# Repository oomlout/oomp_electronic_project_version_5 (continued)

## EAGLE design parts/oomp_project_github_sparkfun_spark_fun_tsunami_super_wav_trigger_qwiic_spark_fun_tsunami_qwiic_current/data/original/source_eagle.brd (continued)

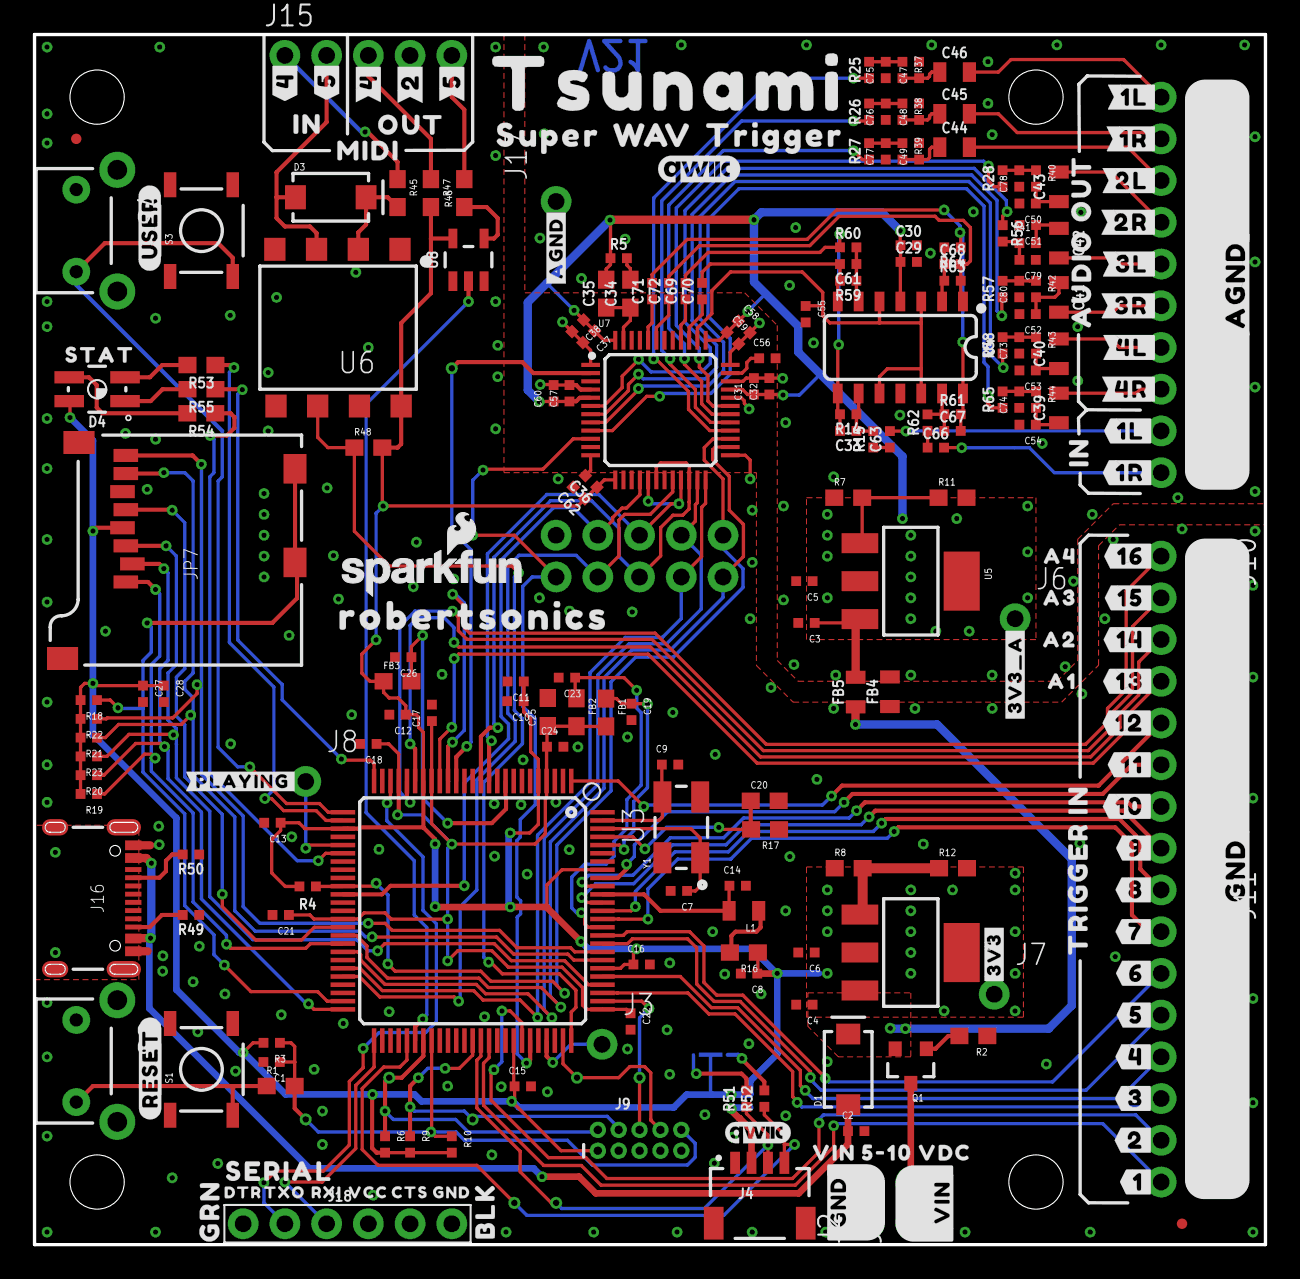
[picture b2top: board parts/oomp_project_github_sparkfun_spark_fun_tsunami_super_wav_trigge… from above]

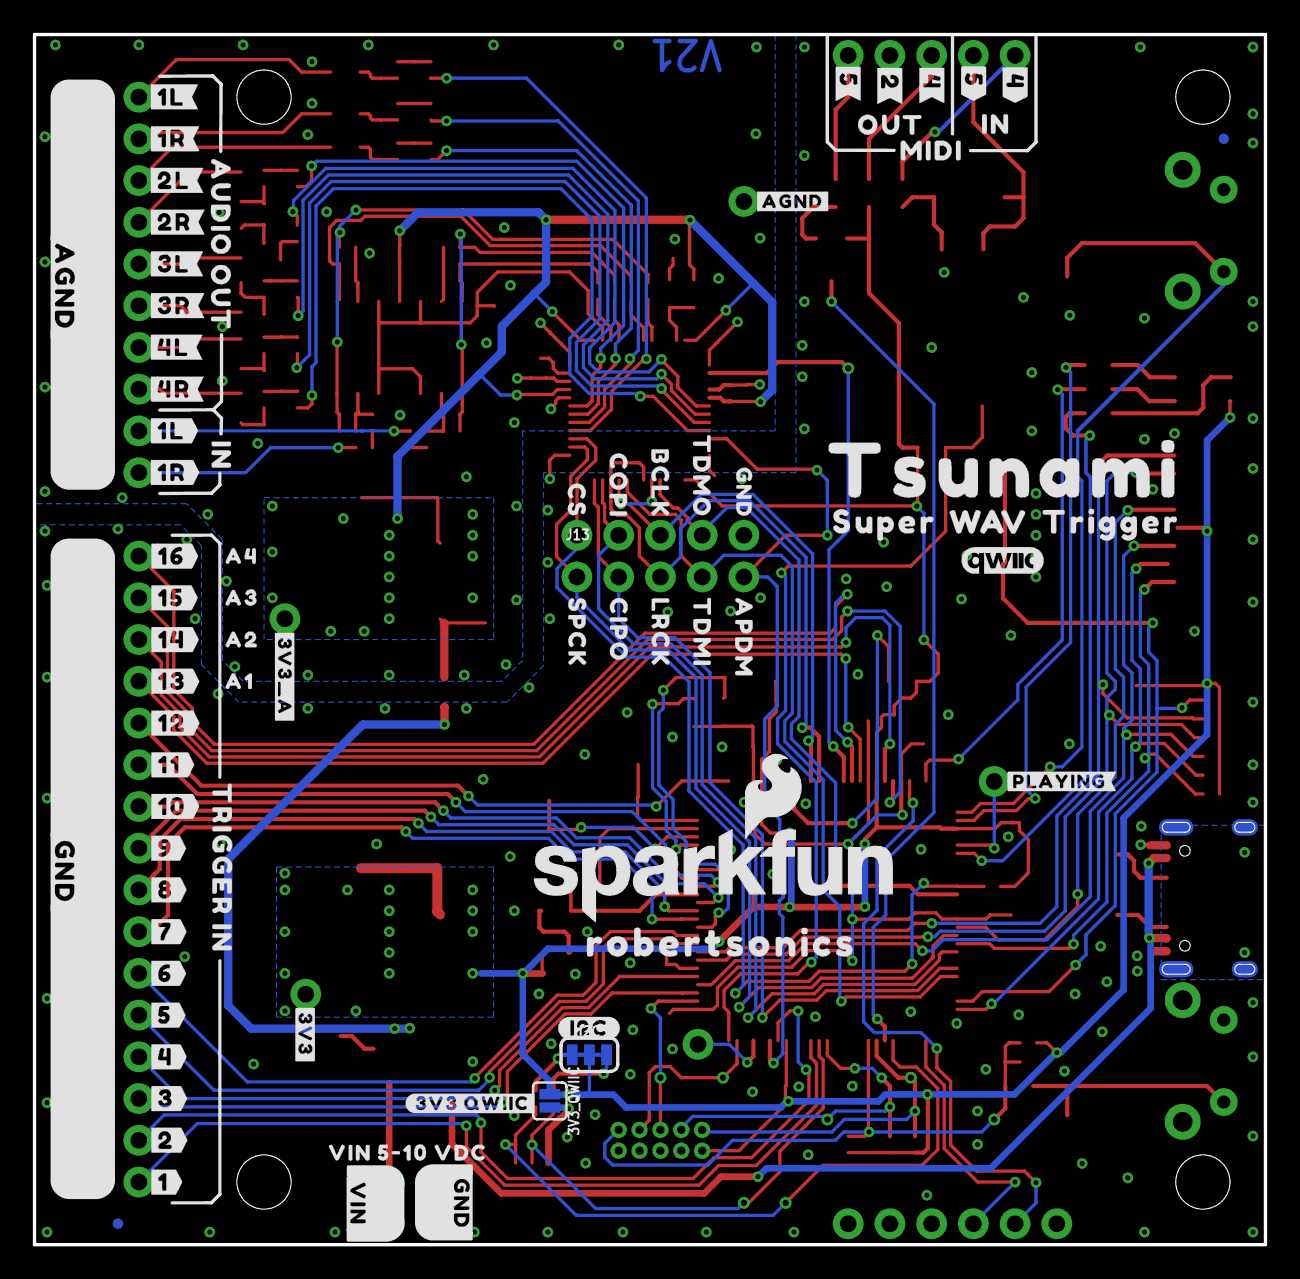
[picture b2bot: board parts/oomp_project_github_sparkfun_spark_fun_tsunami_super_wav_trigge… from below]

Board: 2 copper layers, 74.9 x 73.7 mm, 327 parts (76 on the bottom side), 138 nets.

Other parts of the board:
U$3: GND_0
U$4, U$73: QWIIC_5MM
U$5: STAT0
U$6: #USER#0
U$7: #RESET#0
U$8, U$9: ROBERTSONICS0
U$10, U$167: #2L#0
U$11: #1L#0
U$12, U$120: #1R#0
U$13: #2R#0
U$14: #3R#0
U$15: #3L#0
U$16: #4L#0
U$17: #4R#0
U$18: #4#3
U$19: #2#5
U$20, U$107: AUDIO_OUT0
U$21, U$46, U$108, U$123: IN0
U$22, U$106: TRIGGER_IN0
U$23, U$85: #GND#0
U$24: #1#0
U$25: SERIAL3
U$26, U$60: SUPER0
U$27, U$99: VIN_5#10_VDC0
U$28, U$84: #AGND#0
U$29: #2#0
U$30: #3#0
U$31, U$56, U$117: #4#0
U$32, U$58, U$118: #5#0
U$33: #6#0
U$34: #7#0
U$35: #8#0
U$36: #9#0
U$37: #10#0
U$38: #11#0
U$39: #12#0
U$40: #PLAYING#30
U$41, U$112: #3V3#0
U$43: #13#0
U$44: #3V3_A#0
U$45, U$122: MIDI0
U$47, U$124: OUT0
U$48: #14#0
U$49: #15#0
U$50: #16#0
U$51: A10
U$52: A20
U$53: A30
U$54: A40
U$55: #5#6
U$57: #2#6
U$59: #4#6
U$61, U$110: #GND#1
U$62, U$68: TRIGGER0
U$63, U$69: TSUNAMI0
U$64, U$70: W0
U$65, U$71: A0
U$66, U$72: V0
U$67, U$111: #VIN#2
U$74: #16#5
U$75: #15#17
U$76: #14#17
U$77: #13#17
U$78: #12#17
U$79: #11#17
U$80: #10#17
U$81: #9#17
U$82: #8#17
U$83: #7#17
U$86: CS17
U$87: BCLK19
U$88: COPI18
U$89: TDMO20
U$91: SPCK22
U$92: TDMI25
U$93: LRCK24
U$94: CIPO23
U$95: APDM26
U$96: #AGND#27
U$97: #AGND#28
U$98: #PLAYING#29
U$102: A117
U$103: A2118
U$104: A32119
U$105: A432120
U$113: #I2C#6
U$116: #1L#3
U$119: #1L#6
U$121: #1R#2
U$141: SFE_LOGO_NAME_FLAME_.1
U$162: #3V3_A#4
U$163: #3V3_QWIIC#0
U$164: #1R#3
U$165: #5#5
U$166: #1L#2
U$168: #2R#3
U$169: #3L#3
U$170: #3R#4
U$171: #4L#4
U$172: #4R#5
U$173: #6#17
U$174: #5#17
U$175: #4#17
U$176: #3#17
U$177: #2#17
U$178: #1#17

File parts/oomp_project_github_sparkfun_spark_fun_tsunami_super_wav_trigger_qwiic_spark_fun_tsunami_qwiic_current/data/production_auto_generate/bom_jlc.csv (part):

Comment,Designator,Footprint,LCSC Part #
,U$24,SparkFun_Tsunami_Qwiic-import-fps:#1#0,
,U$178,SparkFun_Tsunami_Qwiic-import-fps:#1#17,
,U$37,SparkFun_Tsunami_Qwiic-import-fps:#10#0,
,U$80,SparkFun_Tsunami_Qwiic-import-fps:#10#17,
,U$38,SparkFun_Tsunami_Qwiic-import-fps:#11#0,
,U$79,SparkFun_Tsunami_Qwiic-import-fps:#11#17,
,U$39,SparkFun_Tsunami_Qwiic-import-fps:#12#0,
,U$78,SparkFun_Tsunami_Qwiic-import-fps:#12#17,
,U$43,SparkFun_Tsunami_Qwiic-import-fps:#13#0,
,U$77,SparkFun_Tsunami_Qwiic-import-fps:#13#17,
,U$48,SparkFun_Tsunami_Qwiic-import-fps:#14#0,
,U$76,SparkFun_Tsunami_Qwiic-import-fps:#14#17,
,U$49,SparkFun_Tsunami_Qwiic-import-fps:#15#0,
,U$75,SparkFun_Tsunami_Qwiic-import-fps:#15#17,
,U$50,SparkFun_Tsunami_Qwiic-import-fps:#16#0,
,U$74,SparkFun_Tsunami_Qwiic-import-fps:#16#5,
,U$11,SparkFun_Tsunami_Qwiic-import-fps:#1L#0,
,U$166,SparkFun_Tsunami_Qwiic-import-fps:#1L#2,
,U$116,SparkFun_Tsunami_Qwiic-import-fps:#1L#3,
,U$119,SparkFun_Tsunami_Qwiic-import-fps:#1L#6,
,"U$12,U$120",SparkFun_Tsunami_Qwiic-import-fps:#1R#0,
,U$121,SparkFun_Tsunami_Qwiic-import-fps:#1R#2,
,U$164,SparkFun_Tsunami_Qwiic-import-fps:#1R#3,
,U$29,SparkFun_Tsunami_Qwiic-import-fps:#2#0,
,U$177,SparkFun_Tsunami_Qwiic-import-fps:#2#17,
,U$19,SparkFun_Tsunami_Qwiic-import-fps:#2#5,
,U$57,SparkFun_Tsunami_Qwiic-import-fps:#2#6,
,"U$10,U$167",SparkFun_Tsunami_Qwiic-import-fps:#2L#0,
,U$13,SparkFun_Tsunami_Qwiic-import-fps:#2R#0,
,U$168,SparkFun_Tsunami_Qwiic-import-fps:#2R#3,
,U$30,SparkFun_Tsunami_Qwiic-import-fps:#3#0,
,U$176,SparkFun_Tsunami_Qwiic-import-fps:#3#17,
,U$15,SparkFun_Tsunami_Qwiic-import-fps:#3L#0,
,U$169,SparkFun_Tsunami_Qwiic-import-fps:#3L#3,
,U$14,SparkFun_Tsunami_Qwiic-import-fps:#3R#0,
,U$170,SparkFun_Tsunami_Qwiic-import-fps:#3R#4,
,"U$41,U$112",SparkFun_Tsunami_Qwiic-import-fps:#3V3#0,
,U$44,SparkFun_Tsunami_Qwiic-import-fps:#3V3_A#0,
,U$162,SparkFun_Tsunami_Qwiic-import-fps:#3V3_A#4,
,U$163,SparkFun_Tsunami_Qwiic-import-fps:#3V3_QWIIC#0,
,"U$31,U$56,U$117",SparkFun_Tsunami_Qwiic-import-fps:#4#0,
,U$175,SparkFun_Tsunami_Qwiic-import-fps:#4#17,
,U$18,SparkFun_Tsunami_Qwiic-import-fps:#4#3,
,U$59,SparkFun_Tsunami_Qwiic-import-fps:#4#6,
,U$16,SparkFun_Tsunami_Qwiic-import-fps:#4L#0,
,U$171,SparkFun_Tsunami_Qwiic-import-fps:#4L#4,
,U$17,SparkFun_Tsunami_Qwiic-import-fps:#4R#0,
,U$172,SparkFun_Tsunami_Qwiic-import-fps:#4R#5,
,"U$32,U$58,U$118",SparkFun_Tsunami_Qwiic-import-fps:#5#0,
,U$174,SparkFun_Tsunami_Qwiic-import-fps:#5#17,
,U$165,SparkFun_Tsunami_Qwiic-import-fps:#5#5,
,U$55,SparkFun_Tsunami_Qwiic-import-fps:#5#6,
,U$33,SparkFun_Tsunami_Qwiic-import-fps:#6#0,
,U$173,SparkFun_Tsunami_Qwiic-import-fps:#6#17,
,U$34,SparkFun_Tsunami_Qwiic-import-fps:#7#0,
,U$83,SparkFun_Tsunami_Qwiic-import-fps:#7#17,
,U$35,SparkFun_Tsunami_Qwiic-import-fps:#8#0,
,U$82,SparkFun_Tsunami_Qwiic-import-fps:#8#17,
,U$36,SparkFun_Tsunami_Qwiic-import-fps:#9#0,
,U$81,SparkFun_Tsunami_Qwiic-import-fps:#9#17,
,"U$28,U$84",SparkFun_Tsunami_Qwiic-import-fps:#AGND#0,
,U$96,SparkFun_Tsunami_Qwiic-import-fps:#AGND#27,
,U$97,SparkFun_Tsunami_Qwiic-import-fps:#AGND#28,
,"U$23,U$85",SparkFun_Tsunami_Qwiic-import-fps:#GND#0,
,"U$61,U$110",SparkFun_Tsunami_Qwiic-import-fps:#GND#1,
,U$113,SparkFun_Tsunami_Qwiic-import-fps:#I2C#6,
,U$98,SparkFun_Tsunami_Qwiic-import-fps:#PLAYING#29,
,U$40,SparkFun_Tsunami_Qwiic-import-fps:#PLAYING#30,
,U$7,SparkFun_Tsunami_Qwiic-import-fps:#RESET#0,
,U$6,SparkFun_Tsunami_Qwiic-import-fps:#USER#0,
,"U$67,U$111",SparkFun_Tsunami_Qwiic-import-fps:#VIN#2,
,J13,SparkFun_Tsunami_Qwiic-import-fps:2X5_NOSILK,
,J18,SparkFun_Tsunami_Qwiic-import-fps:6_PIN_SERIAL_TARGET_SIDE_W_SILK,
,"U$65,U$71",SparkFun_Tsunami_Qwiic-import-fps:A0,
,U$51,SparkFun_Tsunami_Qwiic-import-fps:A10,
,U$102,SparkFun_Tsunami_Qwiic-import-fps:A117,
,U$52,SparkFun_Tsunami_Qwiic-import-fps:A20,
,U$103,SparkFun_Tsunami_Qwiic-import-fps:A2118,
,U$53,SparkFun_Tsunami_Qwiic-import-fps:A30,
,U$104,SparkFun_Tsunami_Qwiic-import-fps:A32119,
,U$54,SparkFun_Tsunami_Qwiic-import-fps:A40,
,U$105,SparkFun_Tsunami_Qwiic-import-fps:A432120,
,U$95,SparkFun_Tsunami_Qwiic-import-fps:APDM26,
,"U$20,U$107",SparkFun_Tsunami_Qwiic-import-fps:AUDIO_OUT0,
,U$87,SparkFun_Tsunami_Qwiic-import-fps:BCLK19,
,U$94,SparkFun_Tsunami_Qwiic-import-fps:CIPO23,
,U$88,SparkFun_Tsunami_Qwiic-import-fps:COPI18,
,U$86,SparkFun_Tsunami_Qwiic-import-fps:CS17,
,U$3,SparkFun_Tsunami_Qwiic-import-fps:GND_0,
,"U$21,U$46,U$108,U$123",SparkFun_Tsunami_Qwiic-import-fps:IN0,
,U$93,SparkFun_Tsunami_Qwiic-import-fps:LRCK24,
,"U$45,U$122",SparkFun_Tsunami_Qwiic-import-fps:MIDI0,
,"U$47,U$124",SparkFun_Tsunami_Qwiic-import-fps:OUT0,
,"U$4,U$73",SparkFun_Tsunami_Qwiic-import-fps:QWIIC_5MM,
,"U$8,U$9",SparkFun_Tsunami_Qwiic-import-fps:ROBERTSONICS0,
,U$25,SparkFun_Tsunami_Qwiic-import-fps:SERIAL3,
,U$141,SparkFun_Tsunami_Qwiic-import-fps:SFE_LOGO_NAME_FLAME_.1,
,UNK3V3_QWIIC0,SparkFun_Tsunami_Qwiic-import-fps:SMT-JUMPER_2_NO_SILK,
,I2C0,SparkFun_Tsunami_Qwiic-import-fps:SMT-JUMPER_3_2-NC_TRACE_SILK,
,U$91,SparkFun_Tsunami_Qwiic-import-fps:SPCK22,
,U$5,SparkFun_Tsunami_Qwiic-import-fps:STAT0,
,"U$26,U$60",SparkFun_Tsunami_Qwiic-import-fps:SUPER0,
,U$92,SparkFun_Tsunami_Qwiic-import-fps:TDMI25,
,U$89,SparkFun_Tsunami_Qwiic-import-fps:TDMO20,
,"U$62,U$68",SparkFun_Tsunami_Qwiic-import-fps:TRIGGER0,
,"U$22,U$106",SparkFun_Tsunami_Qwiic-import-fps:TRIGGER_IN0,
,"U$63,U$69",SparkFun_Tsunami_Qwiic-import-fps:TSUNAMI0,
,"U$66,U$72",SparkFun_Tsunami_Qwiic-import-fps:V0,
,"U$27,U$99",SparkFun_Tsunami_Qwiic-import-fps:VIN_5#10_VDC0,
,"U$64,U$70",SparkFun_Tsunami_Qwiic-import-fps:W0,
0.1uF,"C3,C4,C8,C10,C12,C13,C15,C16,C17,C18,C19,C21,C22,C23,C24,C26,C28,C29,C31,C36,C37,C47,C48,C49,C50,C51,C52,C53,C54,C55,C56,C57,C59,C73,C74,C75,C76,C77,C78,C79,C80",SparkFun_Tsunami_Qwiic-import-fps:0402-TIGHT,C60474
1.0uF,"C30,C32,C38,C58,C60,C62,C63,C66,C69,C70,C71,C72",SparkFun_Tsunami_Qwiic-import-fps:0402-TIGHT,C2887021
100,"R53,R54",SparkFun_Tsunami_Qwiic-import-fps:0603,C22775
100k,"R6,R9,R10,R19,R20,R21,R22",SparkFun_Tsunami_Qwiic-import-fps:0402-TIGHT,C25530
100pF,"C33,C61,C67,C68",SparkFun_Tsunami_Qwiic-import-fps:0402-TIGHT,
10k,"R3,R4,R18,R23",SparkFun_Tsunami_Qwiic-import-fps:0402-TIGHT,C2906861
10nF,C1,SparkFun_Tsunami_Qwiic-import-fps:0402-TIGHT,C5137480
10pF,C20,SparkFun_Tsunami_Qwiic-import-fps:0603,
10uF,"C2,C5,C6,C11,C27",SparkFun_Tsunami_Qwiic-import-fps:0402-TIGHT,C15525
10μH,L1,SparkFun_Tsunami_Qwiic-import-fps:0805,
10Ω,"R25,R26,R27,R28,R37,R38,R39,R40,R41,R42,R43,R44,R56,R57,R58,R65",SparkFun_Tsunami_Qwiic-import-fps:0402-TIGHT,C138066
11.2896 MHz,Y1,SparkFun_Tsunami_Qwiic-import-fps:CRYSTAL-OSC-SMD-5X3,
12pF,"C7,C9",SparkFun_Tsunami_Qwiic-import-fps:0402-TIGHT,
1A/40V/500mV,"D1,D3",SparkFun_Tsunami_Qwiic-import-fps:SMA-DIODE,
1M,R2,SparkFun_Tsunami_Qwiic-import-fps:0603,C2907003
2.2,R16,SparkFun_Tsunami_Qwiic-import-fps:0603,
2.2k,"R51,R52",SparkFun_Tsunami_Qwiic-import-fps:0402-TIGHT,C2906920
2.2uF,C25,SparkFun_Tsunami_Qwiic-import-fps:0603,C23630
220,"R45,R46,R47,R48,R55",SparkFun_Tsunami_Qwiic-import-fps:0603,C2907127
22uF,"C39,C40,C41,C42,C43,C44,C45,C46",SparkFun_Tsunami_Qwiic-import-fps:0805,
240,"R11,R12",SparkFun_Tsunami_Qwiic-import-fps:0603,
3.1A/30V/105mΩ,Q1,SparkFun_Tsunami_Qwiic-import-fps:SOT23-3,
3.3V,J7,SparkFun_Tsunami_Qwiic-import-fps:1X01_NO_SILK,C7501259
3.3VA,J6,SparkFun_Tsunami_Qwiic-import-fps:1X01_NO_SILK,C7501259
33,R1,SparkFun_Tsunami_Qwiic-import-fps:0603,C23140
33k,"R14,R15,R59,R60,R61,R62,R63,R64",SparkFun_Tsunami_Qwiic-import-fps:0402-TIGHT,C2909350
390,"R7,R8",SparkFun_Tsunami_Qwiic-import-fps:0603,C2907031
390nF,C35,SparkFun_Tsunami_Qwiic-import-fps:0603,
4.7uF,C14,SparkFun_Tsunami_Qwiic-import-fps:0402-TIGHT,C368809
470Ω,"FB1,FB2,FB3",SparkFun_Tsunami_Qwiic-import-fps:0603,
5.1k,"R49,R50",SparkFun_Tsunami_Qwiic-import-fps:0402-TIGHT,C25905
5.62k,R17,SparkFun_Tsunami_Qwiic-import-fps:0603,
5.6nF,C34,SparkFun_Tsunami_Qwiic-import-fps:0603,
560Ω,R5,SparkFun_Tsunami_Qwiic-import-fps:0402-TIGHT,C25126
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
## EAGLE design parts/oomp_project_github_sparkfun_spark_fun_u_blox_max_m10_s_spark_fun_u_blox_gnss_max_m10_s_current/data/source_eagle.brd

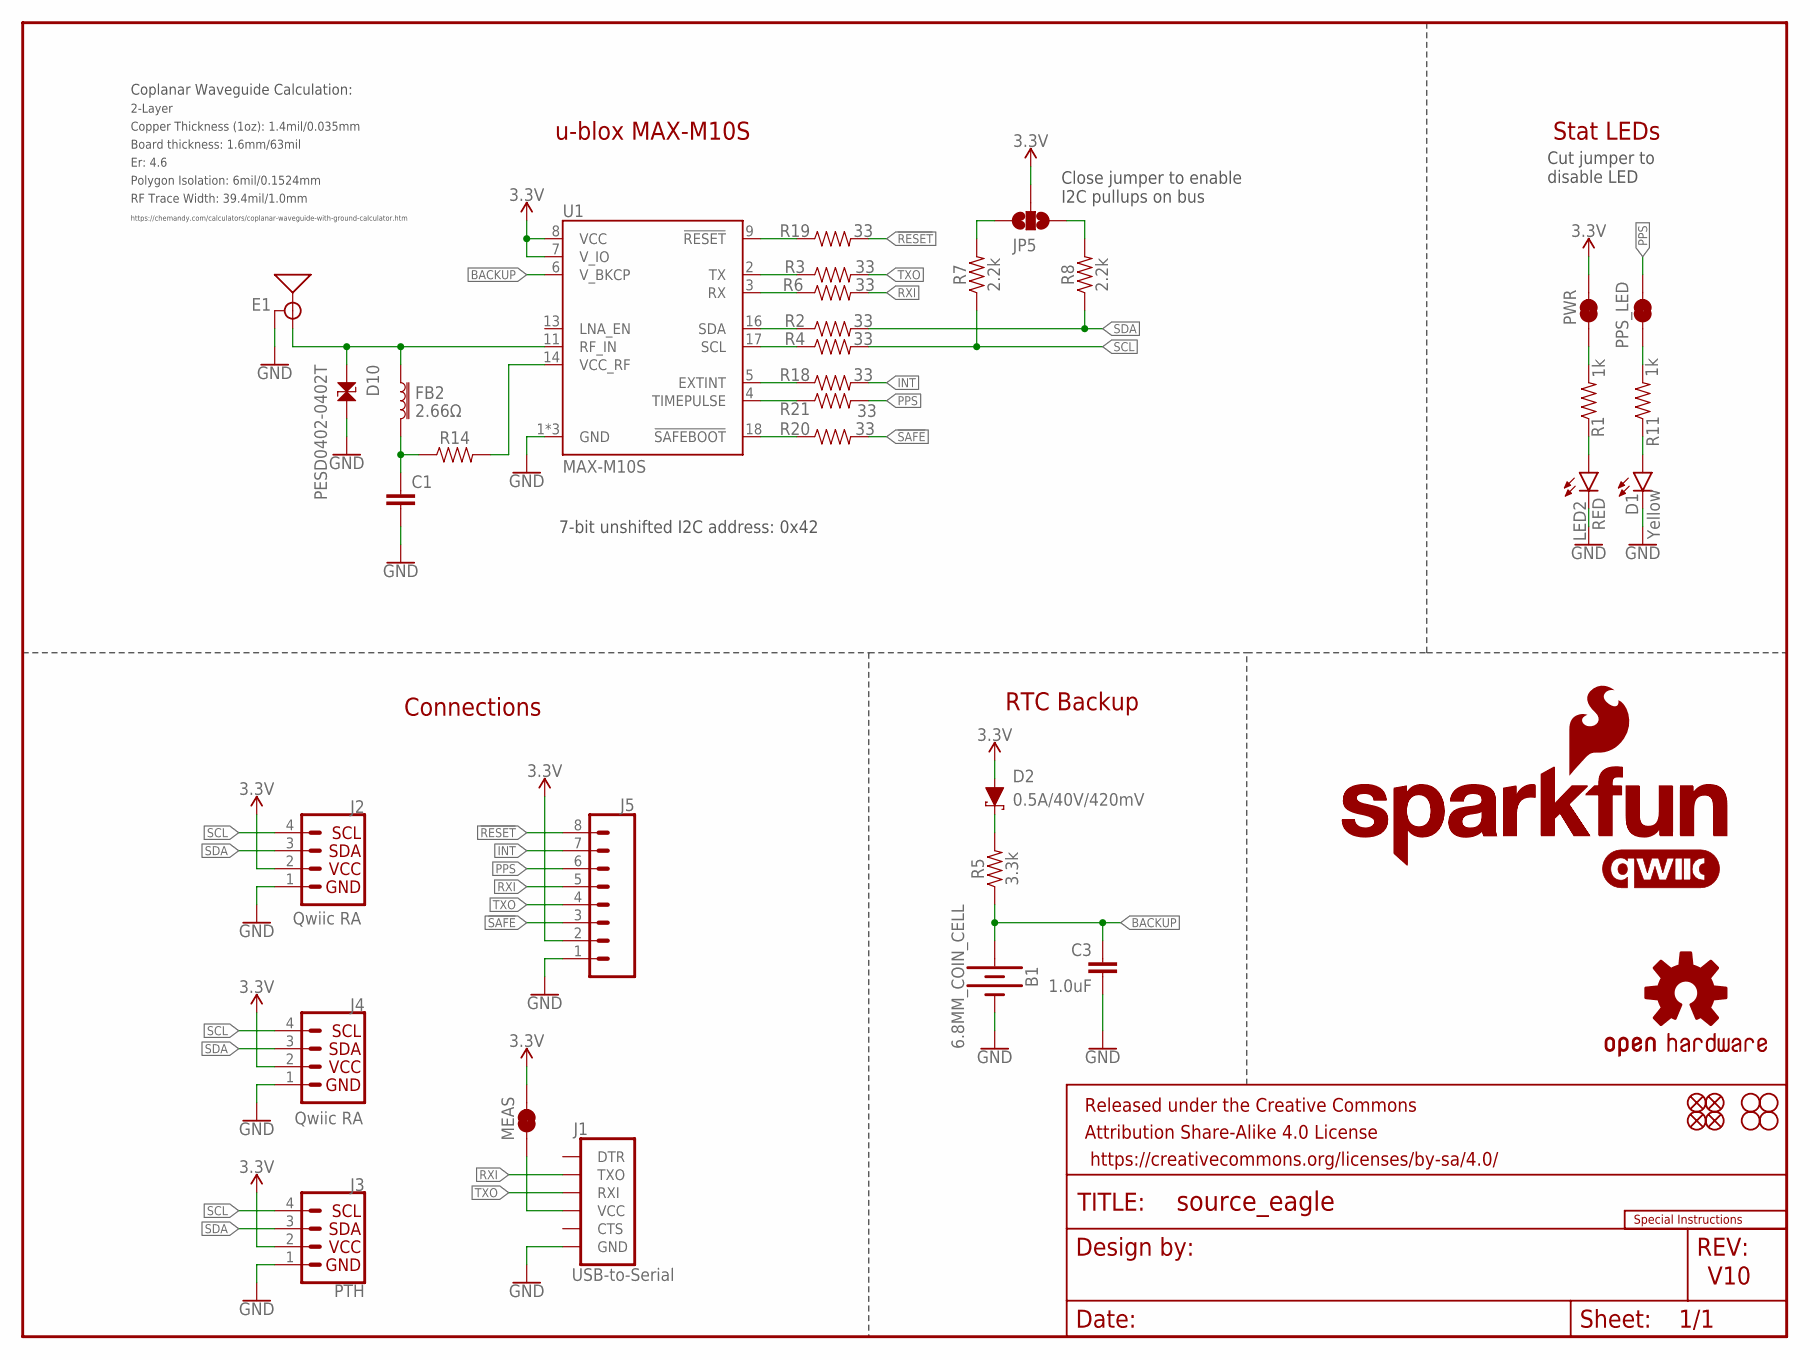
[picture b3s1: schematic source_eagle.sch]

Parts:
B1: 6.8MM_COIN_CELL; ML414H_IV01E
C1: 47pF; 0402-TIGHT
C3: 1.0uF; 0603
D1: Yellow; LED-0603
D2: 0.5A/40V/420mV; SOD-323
D10: PESD0402-0402T; 0402-TIGHT
E1: ANTENNA-SMA-GROUNDEDEDGE_SMA; SMA-EDGE
FB2: 2.66Ω; 0402-TIGHT
FD1, FD2, FD3, FD4: FIDUCIALUFIDUCIAL; FIDUCIAL-MICRO
FRAME1: FRAME-LETTER; CREATIVE_COMMONS
H1, H2, H3, H4: STAND-OFF
J1: USB-to-Serial; 1X06_NO_SILK
J2, J4: Qwiic RA; JST04_1MM_RA
J3: PTH; 1X04_NO_SILK
J5: CONN_08NO_SILK_DNP; 1X08_NO_SILK
JP5: JUMPER-SMT_3_NO_SILK; SMT-JUMPER_3_NO_SILK
LED2: RED; LED-0603
LOGO1: OSHW-LOGOMINI; OSHW-LOGO-MINI
LOGO2: SFE_LOGO_NAME_FLAME.1_INCH; SFE_LOGO_NAME_FLAME_.1
LOGO3: QWIIC_LOGO_5MM; QWIIC_5MM
LOGO4: SFE_LOGO_NAME.1_INCH; SFE_LOGO_NAME_.1
MEAS: JUMPER-COMBO_2_NC_TRACE; COMBO-JUMPER_2_NC_TRACE
PPS_LED: JUMPER-SMT_2_NC_TRACE_SILK; SMT-JUMPER_2_NC_TRACE_SILK
PWR: JUMPER-SMT_2_NC_TRACE_SILK; SMT-JUMPER_2_NC_TRACE_SILK
R1, R11: 1k; 0603
R2, R3, R4, R6, R18, R19, R20, R21: 33; 0603
R5: 3.3k; 0603
R7, R8: 2.2k; 0603
R14: 33OHM-0402T-1/10W-1%; 0402-TIGHT
U1: MAX-M10S
U$2: SPECIAL_INSTRUCTIONS-ORDERING; ORDERING_INSTRUCTIONS

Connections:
3.3V: D2.A, J2.2, J3.2 (VCC), J4.2, J5.2, JP5.2, MEAS.2, MEAS.4 (2), PWR.2, U1.7 (V_IO), U1.8 (VCC)
!RESET: J5.8, R19.2
!SAFE: J5.3, R20.2
ANT_VCC: C1.1, FB2.2, R14.1
BACKUP: B1.+, C3.1, R5.1, U1.6 (V_BKCP)
EXTINT_LV: R18.1, U1.5 (EXTINT)
GND: B1.-, C1.2, C3.2, D1.C, D10.2, E1.GND@0 (GND), E1.GND@1 (GND), E1.GND@2 (GND), E1.GND@3 (GND), J1.6 (GND), J2.1, J3.1 (GND), J4.1, J5.1, LED2.C, U1.1 (GND), U1.10 (GND), U1.12 (GND)
GPS_RF: D10.1, E1.SIG (SIGNAL), FB2.1, U1.11 (RF_IN)
INT: J5.7, R18.2
unnamed: J1.4 (VCC), MEAS.1, MEAS.3 (1)
unnamed: D1.A, R11.1
unnamed: PPS_LED.1, R11.2
unnamed: JP5.1, R8.2
unnamed: D2.C, R5.2
unnamed: JP5.3, R7.2
unnamed: LED2.A, R1.1
unnamed: PWR.1, R1.2
PPS: J5.6, PPS_LED.2, R21.2
PPS_LV: R21.1, U1.4 (TIMEPULSE)
RST_LV: R19.1, U1.9 (!RESET!)
RXI: J1.3 (TXO), J5.5, R6.2
RXLV: R6.1, U1.3 (RX)
SAFE_LV: R20.1, U1.18 (!SAFEBOOT!)
SCL: J2.4, J3.4 (SCL), J4.4, R4.2, R7.1
SCL_LV: R4.1, U1.17 (SCL)
SDA: J2.3, J3.3 (SDA), J4.3, R2.2, R8.1
SDA_LV: R2.1, U1.16 (SDA)
TXLV: R3.1, U1.2 (TX)
TXO: J1.2 (RXI), J5.4, R3.2
VCC_RF: R14.2, U1.14 (VCC_RF)

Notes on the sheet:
V10
7-bit unshifted I2C address: 0x42
u-blox MAX-M10S
RTC Backup
Stat LEDs
Close jumper to enable I2C pullups on bus
Cut jumper to disable LED
Coplanar Waveguide Calculation:
Connections
Board thickness: 1.6mm/63mil
Er: 4.6
Copper Thickness (1oz): 1.4mil/0.035mm
RF Trace Width: 39.4mil/1.0mm
Polygon Isolation: 6mil/0.1524mm
2-Layer
https://chemandy.com/calculators/coplanar-waveguide-with-ground-calculator.htm

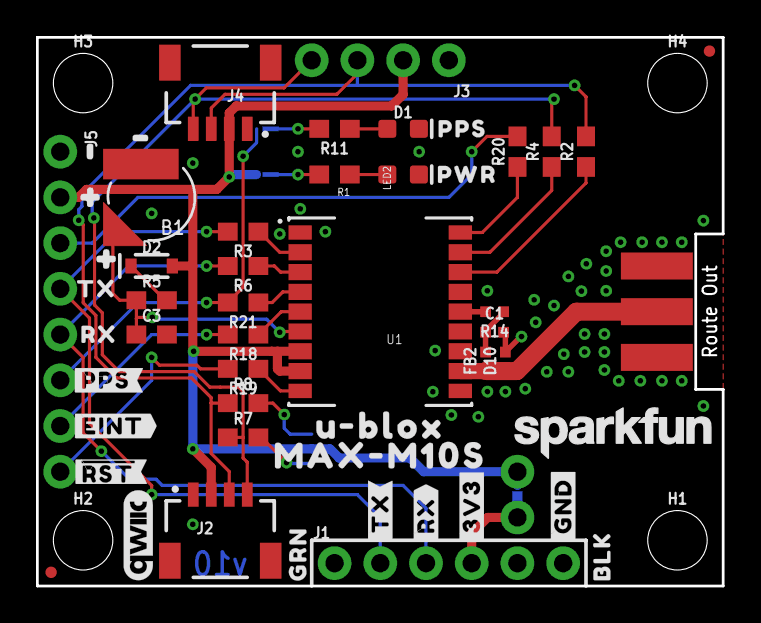
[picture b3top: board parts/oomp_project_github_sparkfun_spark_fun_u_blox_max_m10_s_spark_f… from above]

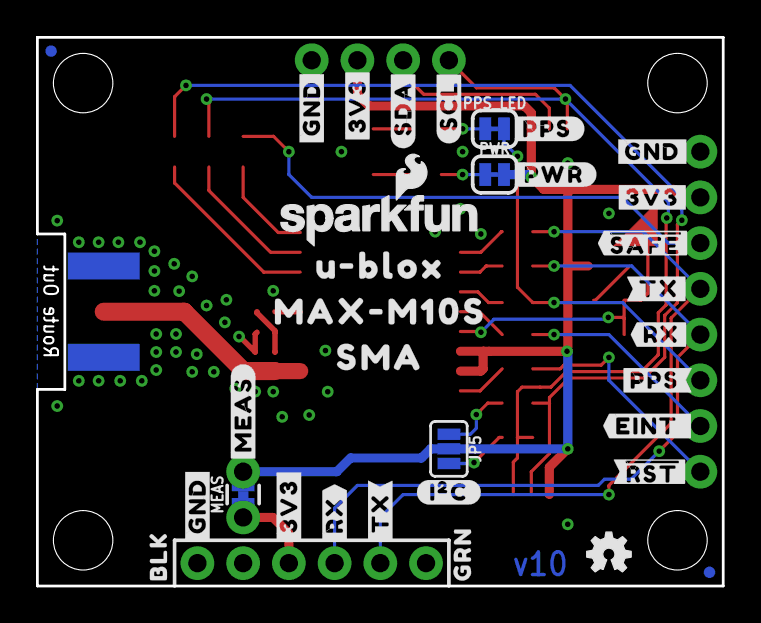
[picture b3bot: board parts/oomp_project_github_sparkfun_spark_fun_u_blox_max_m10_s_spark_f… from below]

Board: 2 copper layers, 38.1 x 30.5 mm, 91 parts (33 on the bottom side), 30 nets.

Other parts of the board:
U$1, U$10, U$26, U$31: #3V3#4
U$3, U$11, U$27, U$34: #GND#5
U$4, U$28: BLK0
U$5, U$29: GRN1
U$6: PPS7
U$7: PWR6
U$8, U$25: #RX#2
U$9, U$22: #TX#3
U$12: ##RST##2
U$13: ##SAFE##0
U$14, U$43: #PPS#1
U$15: #RX#1
U$16: #TX#0
U$18, U$23: MAX#M10S1
U$19, U$37: #0
U$20, U$21: U#BLOX0
U$24: SMA2
U$30: #I�C#0
U$32: #SCL#1
U$33: #SDA#0
U$35: #PPS#0
U$36: #PWR#0
U$38, U$40: #1
U$39: ##RST##0
U$41: #MEAS#0
U$42: #EINT#0
U$44: RX2
U$45: TX3
U$46: #EINT_#0

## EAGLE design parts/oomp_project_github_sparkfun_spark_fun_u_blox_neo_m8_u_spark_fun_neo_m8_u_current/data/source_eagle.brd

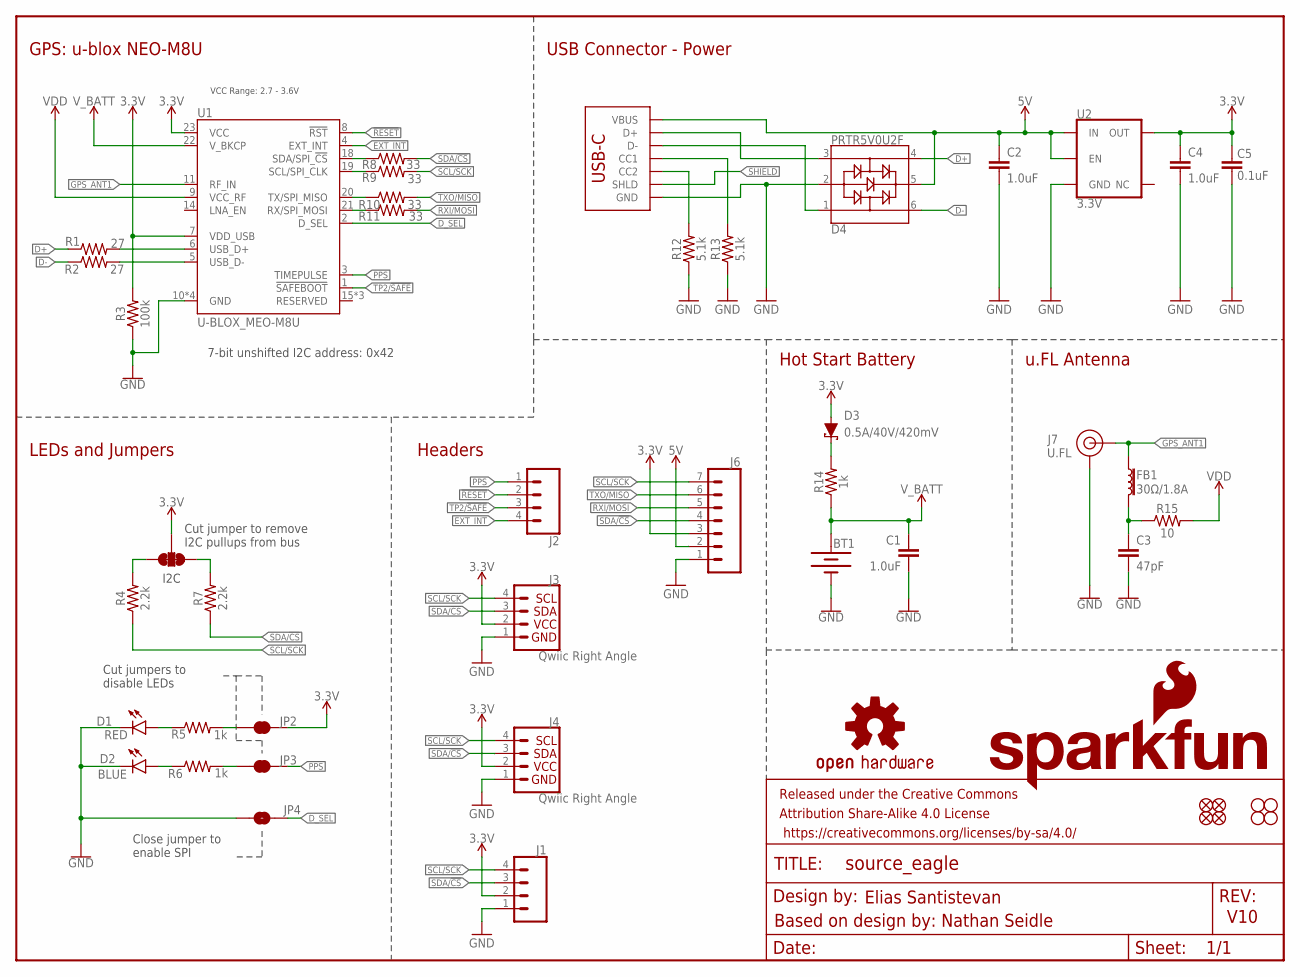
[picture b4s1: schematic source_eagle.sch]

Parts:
BT1: 6.8MM_COIN_CELL; ML414H_IV01E
C1, C2, C4: 1.0uF; 0603
C3: 47pF; 0603
C5: 0.1uF; 0603
D1: RED; LED-0603
D2: BLUE; LED-0603
D3: 0.5A/40V/420mV; SOD-323
D4: PRTR5V0U2F; SOT886
FB1: 30Ω/1.8A; 0603
FRAME1: FRAME-LETTER; CREATIVE_COMMONS
J1, J2: CONN_041X04_NO_SILK; 1X04_NO_SILK
J3, J4: Qwiic Right Angle; JST04_1MM_RA
J5: USB_C_2-LAYER_PADS; USB-C-16P-2LAYER-PADS
J6: CONN_07NO_SILK; 1X07_NO_SILK
J7: U.FL
JP1: JUMPER-SMT_3_2-NC_TRACE_SILK; SMT-JUMPER_3_2-NC_TRACE_SILK
JP2, JP3: JUMPER-SMT_2_NC_TRACE_SILK; SMT-JUMPER_2_NC_TRACE_SILK
JP4: JUMPER-SMT_2_NO_SILK; SMT-JUMPER_2_NO_SILK
JP5, JP6, JP7, JP8: FIDUCIALUFIDUCIAL; MICRO-FIDUCIAL
JP9, JP10, JP11, JP12: STAND-OFF
LOGO1: OSHW-LOGOMINI; OSHW-LOGO-MINI
LOGO2: SFE_LOGO_NAME_FLAME.1_INCH; SFE_LOGO_NAME_FLAME_.1
R1, R2: 27; 0603
R3: 100k; 0603
R4, R7: 2.2k; 0603
R5, R6, R14: 1k; 0603
R8, R9, R10, R11: 33; 0603
R12, R13: 5.1k; 0603
R15: 10; 0603
U1: U-BLOX_MEO-M8U; NEO-M9N/M8T/M8U
U2: 3.3V; SOT23-5

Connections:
3.3V: C4.1, C5.2, D3.A, J1.2, J3.2, J4.2, J6.3, JP1.2, JP2.2, R3.2, U1.7 (VDD_USB), U1.23 (VCC), U2.5 (OUT)
5V: C2.1, D4.5, J5.VBUS1 (VBUS), J5.VBUS2 (VBUS), J6.2, U2.1 (IN), U2.3 (EN)
!RESET: J2.2, U1.8 (!RST)
ANT_VCC: C3.1, FB1.2, R15.1
D+: D4.4, R1.1
D-: D4.6, R2.1
D_SEL: JP4.2, U1.2 (D_SEL)
EXT_INT: J2.4, U1.4 (EXT_INT)
GND: BT1.-, C1.2, C2.2, C3.2, C4.2, C5.1, D1.C, D2.C, D4.2, J1.1, J3.1, J4.1, J5.GND, J5.GND2 (GND), J6.1, J7.1 (GND), J7.2 (GND), JP4.1, R3.1, R12.1, R13.1, U1.10 (GND), U1.12 (GND), U1.13 (GND), U1.24 (GND), U2.2 (GND)
GPS_ANT1: FB1.1, J7.FEED (SIGNAL), U1.11 (RF_IN)
unnamed: JP2.1, R5.2
unnamed: D2.A, R6.1
unnamed: R8.1, U1.18 (SDA/SPI_!CS!)
unnamed: JP3.1, R6.2
unnamed: JP1.1, R7.2
unnamed: D3.C, R14.2
unnamed: J5.B5 (CC2), R12.2
unnamed: JP1.3, R4.2
unnamed: J5.A5 (CC1), R13.2
unnamed: D1.A, R5.1
unnamed: R1.2, U1.6 (USB_D+)
unnamed: R2.2, U1.5 (USB_D-)
unnamed: R9.1, U1.19 (SCL/SPI_CLK)
unnamed: R10.1, U1.20 (TX/SPI_MISO)
unnamed: R11.1, U1.21 (RX/SPI_MOSI)
PPS: J2.1, JP3.2, U1.3 (TIMEPULSE)
RXI/MOSI: J6.5, R11.2
SCL/SCK: J1.4, J3.4, J4.4, J6.7, R4.1, R9.2
SDA/!CS: J1.3, J3.3, J4.3, J6.4, R7.1, R8.2
SHIELD: J5.SHLD1 (SHLD), J5.SHLD2 (SHLD), J5.SHLD3 (SHLD), J5.SHLD4 (SHLD)
TP2/!SAFE: J2.3, U1.1 (!SAFEBOOT!)
TXO/MISO: J6.6, R10.2
USB_D+: D4.3, J5.A6 (D+), J5.B6 (D+)
USB_D-: D4.1, J5.A7 (D-), J5.B7 (D-)
VDD: R15.2, U1.9 (VCC_RF)
V_BATT: BT1.+, C1.1, R14.1, U1.22 (V_BKCP)

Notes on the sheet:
V10
7-bit unshifted I2C address: 0x42
Cut jumper to remove I2C pullups from bus
Cut jumpers to disable LEDs
Close jumper to enable SPI
Elias Santistevan
Headers
LEDs and Jumpers
Hot Start Battery
GPS: u-blox NEO-M8U
u.FL Antenna
USB Connector - Power
Based on design by: Nathan Seidle
VCC Range: 2.7 - 3.6V
I2C

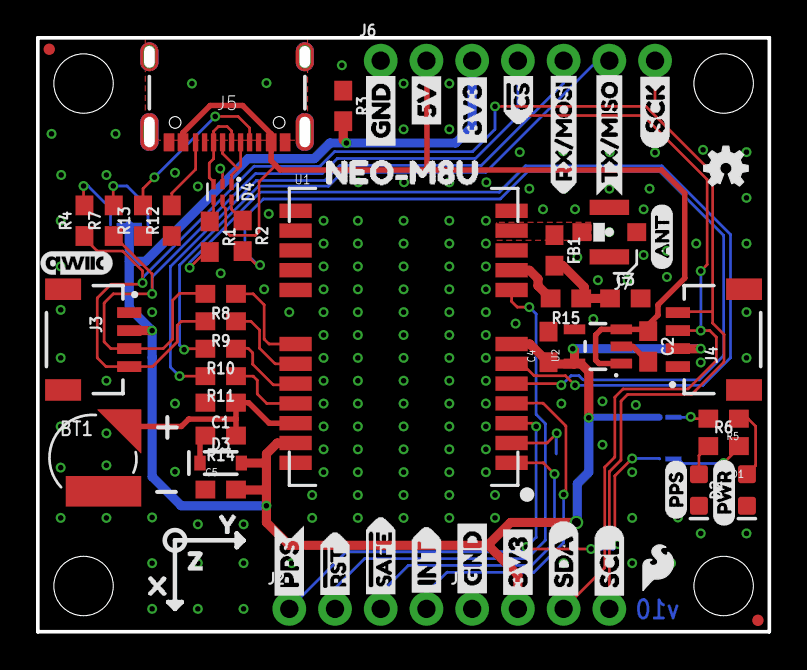
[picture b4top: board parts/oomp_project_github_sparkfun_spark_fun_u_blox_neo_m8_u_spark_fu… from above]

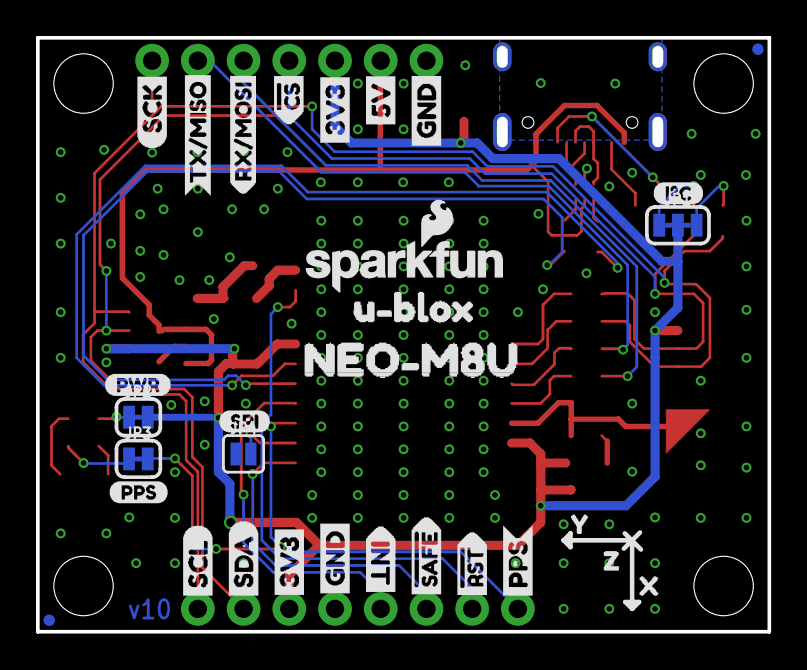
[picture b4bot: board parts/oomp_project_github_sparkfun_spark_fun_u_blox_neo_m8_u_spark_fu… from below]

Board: 2 copper layers, 40.6 x 33.0 mm, 98 parts (31 on the bottom side), 36 nets.

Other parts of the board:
U$1, U$4: SDA-[)
U$2: INT1
U$3, U$5: SCL-[)
U$6, U$7, U$60, U$61: 3V3-04
U$8, U$9, U$62, U$63: GND-04
U$10: I_SUPER2_C-()-03
U$11: SPI1
U$12, U$52: PPS0
U$13, U$16: X1
U$14: QWIIC_4MM
U$15, U$34: NEO#M8U0
U$17: PWR1
U$18: PWR-()-03
U$19, U$20: 5V
U$21, U$27: Y2
U$22: U#BLOX3
U$23, U$24: CS#-<]
U$25: ANT0
U$26, U$31: RX#MOSI3
U$28, U$30: Z0
U$29, U$37: TX#MISO1
U$32: INT0
U$33: SFE_LOGO_FLAME_.1
U$35, U$36: #RST3
U$38, U$41: SCK-(]-04
U$39, U$40: #SAFE1
U$43, U$44: PPS5

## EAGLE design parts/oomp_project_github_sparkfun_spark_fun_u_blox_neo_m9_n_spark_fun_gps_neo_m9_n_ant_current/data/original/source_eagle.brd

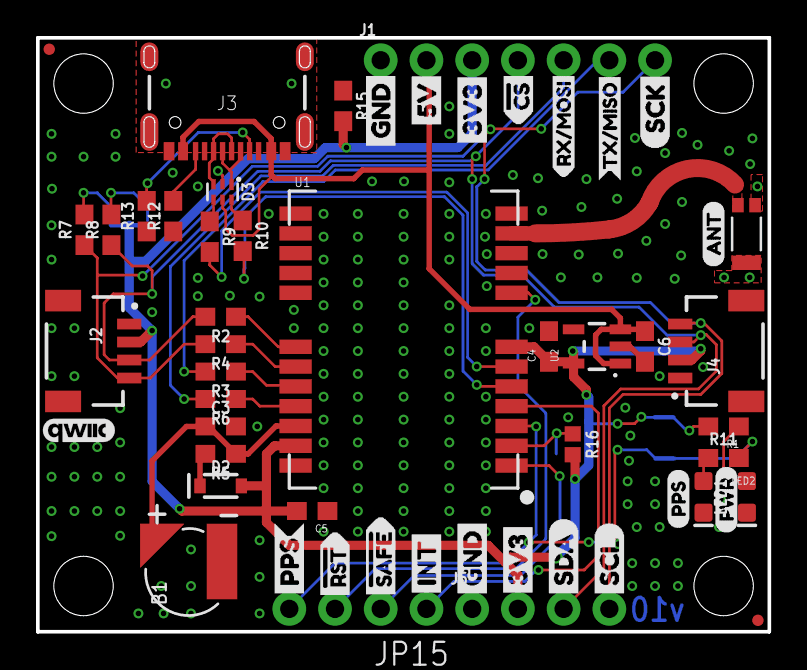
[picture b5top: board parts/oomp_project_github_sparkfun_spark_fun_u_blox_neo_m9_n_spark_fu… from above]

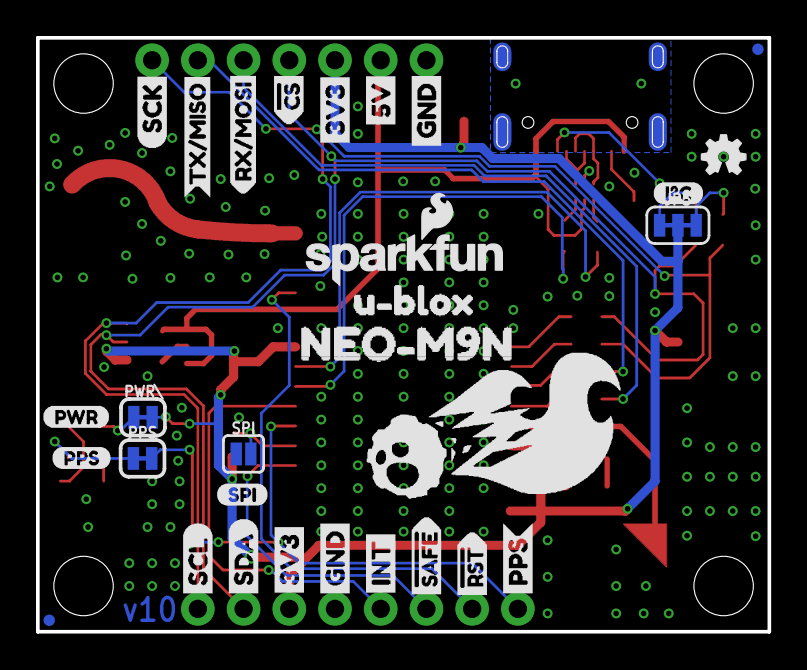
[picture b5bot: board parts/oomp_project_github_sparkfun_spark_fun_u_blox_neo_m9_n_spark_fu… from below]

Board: 2 copper layers, 40.6 x 33.0 mm, 89 parts (30 on the bottom side), 34 nets.

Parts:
B1: 6.8MM_COIN_CELL; ML414H_IV01E
C3, C4, C6: 1.0uF; 0603
C5: 0.1uF; 0603
D2: 0.5A/40V/420mV; SOD-323
D3: PRTR5V0U2F; SOT886
FRAME1: FRAME-LETTER; CREATIVE_COMMONS
J1: 1X07_NO_SILK
J2, J4: Qwiic Right Angle; JST04_1MM_RA
J3: USB-C-16P
J5: 1X04_NO_SILK
JP5: JUMPER-SMT_3_2-NC_TRACE_SILK; SMT-JUMPER_3_2-NC_TRACE_SILK
JP15: 1X04_NO_SILK
JP21, JP61, JP71, JP81: FIDUCIALUFIDUCIAL; MICRO-FIDUCIAL
JP31, JP41, JP91, JP101: STAND-OFF
LED1: BLUE; LED-0603
LED2: RED; LED-0603
LOGO1: OSHW-LOGOMINI; OSHW-LOGO-MINI
LOGO2: SFE_LOGO_NAME_FLAME.1_INCH; SFE_LOGO_NAME_FLAME_.1
PPS: JUMPER-SMT_2_NC_TRACE_SILK; SMT-JUMPER_2_NC_TRACE_SILK
PWR\: JUMPER-SMT_2_NC_TRACE_SILK; SMT-JUMPER_2_NC_TRACE_SILK
R1, R5, R11: 1k; 0603
R2, R3, R4, R6: 33; 0603
R7, R8: 2.2k; 0603
R9, R10: 27; 0603
R12, R13: 5.1k; 0603
R15: 100k; 0603
R16: 10k; 0402
SPI: JUMPER-SMT_2_NO_SILK; SMT-JUMPER_2_NO_SILK
U1: U-BLOX_NEO-M9N; NEO-M9N
U2: 3.3V; SOT23-5
U$1, U$4: SDA-[)
U$2: NEO#M9N1
U$3, U$5: SCL-[)
U$6, U$7, U$60, U$61: 3V3-04
U$8, U$9, U$62, U$63: GND-04
U$10: I_SUPER2_C-()-03
U$11: SPI1
U$12, U$52: PPS0
U$13: ANT0
U$14: QWIIC_4MM
U$15, U$16: INT8
U$17: PWR1
U$18: PWR-()-03
U$19, U$20: 5V
U$21: NEO_GPS_BOARD_SILK_FINAL#03#JPG
U$22: U#BLOX3
U$23, U$24: CS#-<]
U$26: RX#MOSI2
U$31: RX#MOSI3
U$34: TX#MISO0
U$35, U$36: #RST3
U$37: TX#MISO1
U$38, U$41: SCK-(]-04
U$39, U$40: #SAFE1
U$43, U$44: PPS5
Y1: GPS_CHIP_ANTENNAW3011; W3011

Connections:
3.3V: C4.1, C5.2, D2.A, J1.3, J2.2, J4.2, J5.2, JP5.2, PWR\.2, R15.2, R16.2, U1.7, U1.23, U2.5
5V: C6.1, D3.5, J1.2, J3.VBUS1, J3.VBUS2, U2.1, U2.3
!RESET: JP15.3, U1.8
!SAFE: JP15.2, U1.1
BACKUP: B1.+, C3.1, R5.1, U1.22
D+: D3.4, R9.1
D-: D3.6, R10.1
D_SEL: R16.1, SPI.2, U1.2
GND: B1.-, C3.2, C4.2, C5.1, C6.2, D3.2, J1.1, J2.1, J3.GND, J3.GND2, J4.1, J5.1, LED1.C, LED2.C, R12.1, R13.1, R15.1, SPI.1, U1.10, U1.12, U1.13, U1.24, U2.2, Y1.2, Y1.3
GPS_ANT1: U1.11, Y1.1
INT: JP15.1, U1.4
unnamed: PWR\.1, R1.2
unnamed: LED1.A, R11.1
unnamed: PPS.1, R11.2
unnamed: JP5.1, R8.2
unnamed: D2.C, R5.2
unnamed: J3.B5, R12.2
unnamed: JP5.3, R7.2
unnamed: J3.A5, R13.2
unnamed: LED2.A, R1.1
unnamed: R9.2, U1.6
unnamed: R10.2, U1.5
PPS: JP15.4, PPS.2, U1.3
RXI/MOSI: J1.5, R6.2
RXLV: R6.1, U1.21
SCL/SCK: J1.7, J2.4, J4.4, J5.4, R4.2, R7.1
SCL_LV: R4.1, U1.19
SDA/!CS: J1.4, J2.3, J4.3, J5.3, R2.2, R8.1
SDA_LV: R2.1, U1.18
SHLD: J3.SHLD1, J3.SHLD2, J3.SHLD3, J3.SHLD4, J3.SHLD5, J3.SHLD6, J3.SHLD7, J3.SHLD8
TXLV: R3.1, U1.20
TXO/MISO: J1.6, R3.2
USB_D+: D3.3, J3.A6, J3.B6
USB_D-: D3.1, J3.A7, J3.B7
